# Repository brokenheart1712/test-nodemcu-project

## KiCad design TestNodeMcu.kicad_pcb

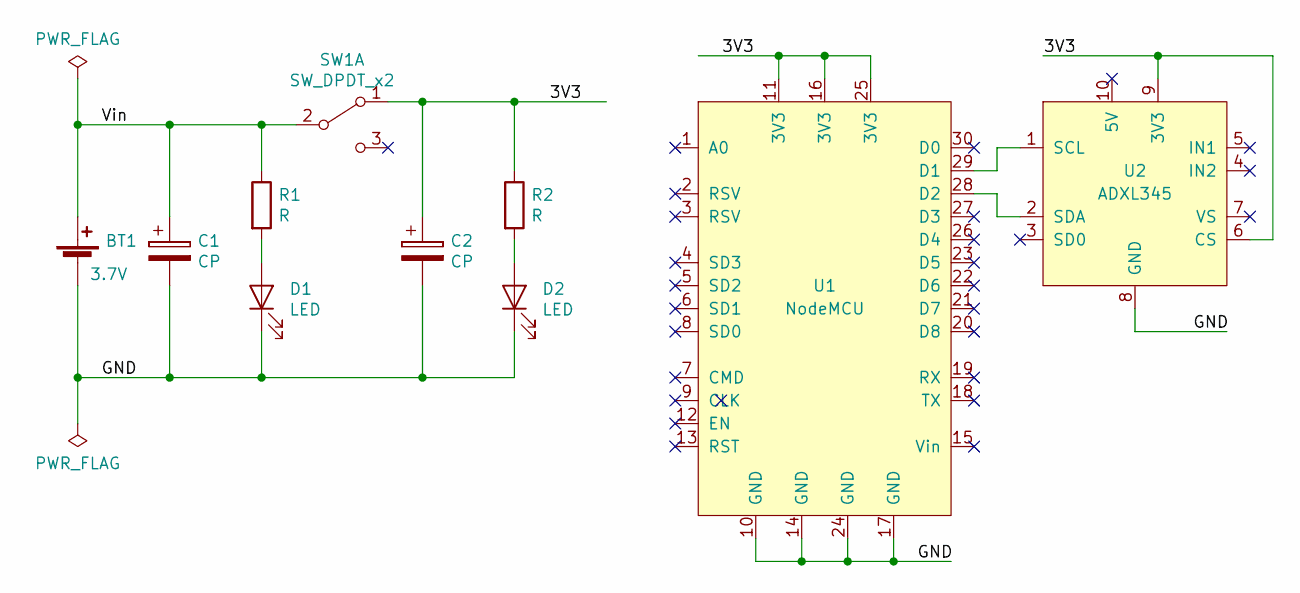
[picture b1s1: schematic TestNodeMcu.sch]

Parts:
BT1: 3.7V; Battery3.7V
C1, C2: CP; CP_Radial_D5.0mm_P2.50mm
D1, D2: LED; LED_D5.0mm
R1, R2: R; R_Axial_DIN0207_L6.3mm_D2.5mm_P7.62mm_Horizontal
SW1: SW_DPDT_x2; Switch_Slide_11.6x4mm_EG1218
U1: NodeMCU; NodeMCUDevKit1.0
U2: ADXL345; ADXL345_Horizontal

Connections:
/3V3: C2.1, R2.1, SW1.1 (A), U1.11 (3V3), U1.16 (3V3), U1.25 (3V3), U2.6 (CS), U2.9 (3V3)
/GND: BT1.2 (-), C1.2, C2.2, D1.1 (K), D2.1 (K), U1.10 (GND), U1.14 (GND), U1.17 (GND), U1.24 (GND), U2.8 (GND)
/Vin: BT1.1 (+), C1.1, R1.1, SW1.2 (B)
unnamed: D1.2 (A), R1.2
unnamed: D2.2 (A), R2.2
unnamed: U1.28 (D2), U2.2 (SDA)
unnamed: U1.29 (D1), U2.1 (SCL)

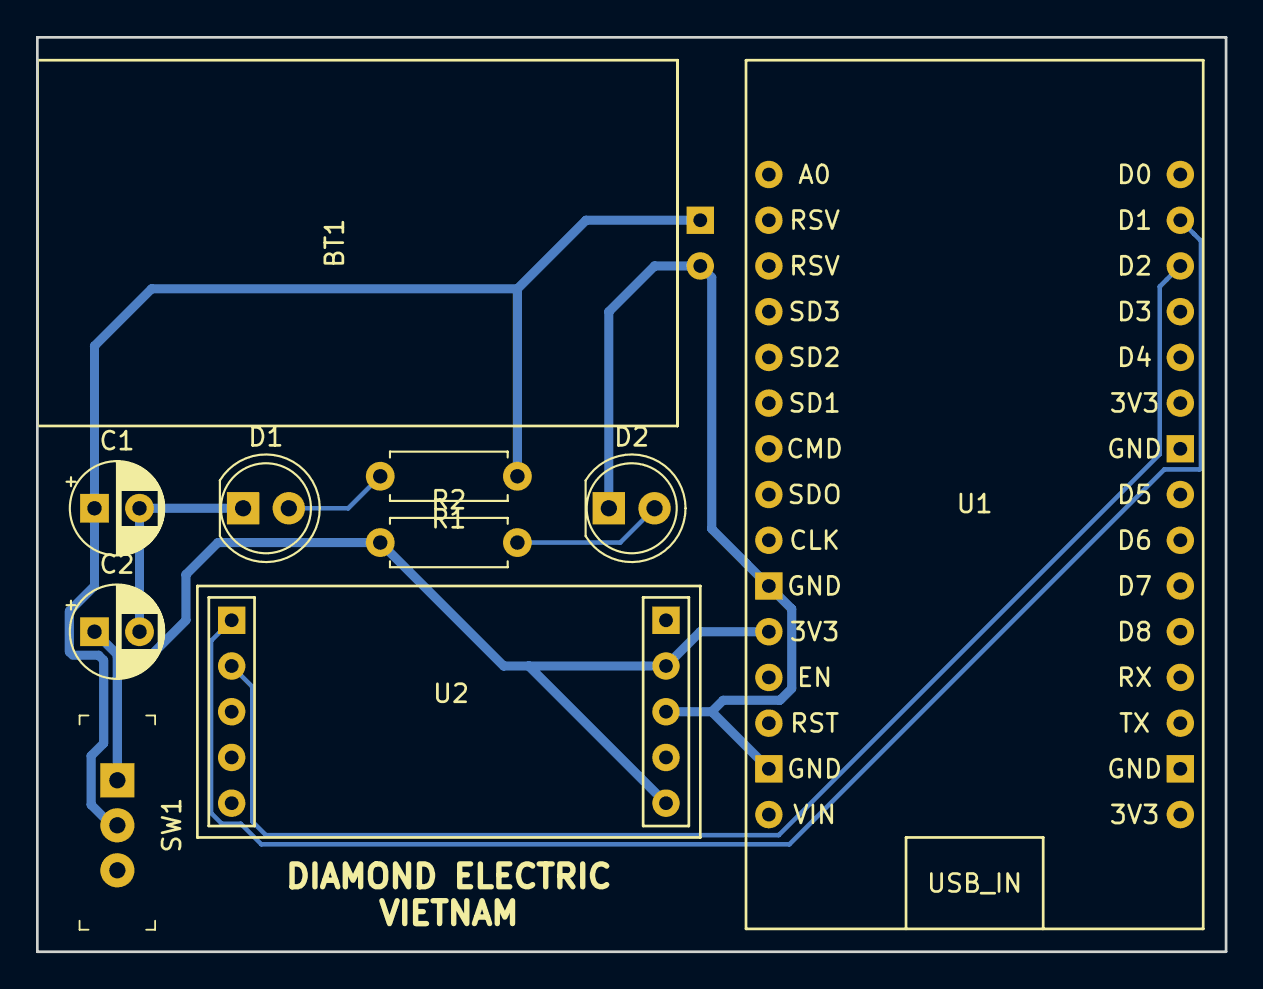
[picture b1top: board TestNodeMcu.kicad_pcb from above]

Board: 2 copper layers, 66.0 x 50.8 mm, 10 parts (0 on the bottom side), 7 nets.
